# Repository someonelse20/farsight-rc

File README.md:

# Farsight RC

Custom long range remote controller with ESP32 to stream telemetry and an STM32 based lora module with the SX1262. The controller has a build in 18650 battery with an integrated charger. The transceiver is its own standalone board and can be used independenly of the controller. I made this project as a part of my larger goal to make a custom drone. I originally was going to make it out of stock modules but decided to design custom pcbs.

## Usage

**--This is still under development and is subject to change--**

### Controller

The switch in the middle of the controller is the power switch and the led is the status of the battery charging. The usb connecter will charge the battery and can be used to communicate with the ESP32. The micro SD card will log all the incoming telemetry.

The controller software is currently pretty basic and missing some fetures. The wifi network the esp32 will create can be configured by installing the espressive ide and running idf.py menuconfig and changing the wifi ssid and password under Wifi Configuration. Requesting /telemetry of the ip of the nextork will return a set of comma separated values in the format of "altitude_meters,speed_meters_per_second,heading_degrees,latitude,longitude".

### Transceiver

UART pinout:
| 1 | 2 | 3 | 4 |
|-----|-----|----|----|
| VCC | GND | RX | TX |

Microcontroller pinout:
| 1 | 2 |
|-------|------|
| RESET | BOOT |

Debug pinout:
| 1 | 2 |
|--------|-------|
| SWDCLK | SWDIO |

The transceiver has an internal regulator and can handle up to 5v input. The UART pinout is from the transceiver reference so an external device would put its Tx to the transceiver Rx and vice versa. The buttons on the board will put the STM32 into boot and reset mode respectively and the external pins are directly wired to the microcontroller.

The transceiver is built on the [Semtech SX1262 driver](https://github.com/Lora-net/sx126x_driver). To communicate with the transceiver a host must first send a register bit and then the data to transmit or receive based on the table below.
| Address | Name | Description | Input/Output | Size | Note |
|---------|--------------------------|------------------------------------|--------------|------|-------------------------------------------------------------------------------------------------------------------------------------------------------------------------|
| 0 | who_am_i | Device ID | O | 1 | Device ID is 126 |
| 1 | TX | Transmits packet | I | - | First send size byte then send data byte. |
| 2 | RX | Receives packet | I/O | - | First send size byte then send data byte. |
| 3 | TX_set | Transmits packet | I | - | Packet size must always be payload_len. |
| 4 | RX_set | Receives packet | O | - | Packet size must always be payload_len. |
| 5 | sleep | Puts transceiver into sleep mode | - | 0 | |
| 6 | wakeup | Wakes up transceiver | - | 0 | |
| 7 | set_all | Inputs a setting struct | I | TBD | See [settings_t](https://github.com/someonelse20/remote-controller/blob/main/software/transceiver/Core/Inc/uart_reg.h#L29) |
| 8 | set_frequency | Sets SX1262 frequency | I | 4 | See [sx126x_set_rf_freq](https://github.com/Lora-net/sx126x_driver/blob/master/src/sx126x.h#L1084) |
| 9 | set_tx_params | Sets SX1262 TX power and ramp time | I | 2 | array of {power in dBm, ramp time ([see datasheet](https://semtech.my.salesforce.com/sfc/p/#E0000000JelG/a/RQ000008nKCH/hp2iKwMDKWl34g1D3LBf_zC7TGBRIo2ff5LMnS8r19s]))} |
| 10 | set_lora_mod_params | Sets LoRa parameters | I | TBD | See [sx126x_mod_params_lora_t](https://github.com/Lora-net/sx126x_driver/blob/master/src/sx126x.h#L381) |
| 11 | set_lora_pkt_params | Sets LoRa packet parameters | I | TBD | See [sx126x_pkt_params_lora_t](https://github.com/Lora-net/sx126x_driver/blob/master/src/sx126x.h#L454) |
| 12 | set_lora_symb_nb_timeout | Sets loRa timeout in symbols | I | 1 | See [sx126x_set_lora_symb_nb_timeout](https://github.com/Lora-net/sx126x_driver/blob/master/src/sx126x.h#L1236) |
| 13 | set_encrypt_params | Sets encryption parameters | I | - | Not currently implemented |
| 14 | enable_encrypt | Enables/disables encryption | I | - | Not currently implemented |

TBD means that the size is based on the size of a struct which will be calculated when I can run the code on the hardware.

## BOM

BOM to make two transceivers and two controllers but with only two antennas and one micro SD card.
All prices in USD. Price column is total price and does not include shipping.
| Item | Quantity | Price | Link |
|------------------|----------|-------|--------------------------------------------------------------------------------------------------------|
| Controller pcb | 2 | 49.99 | https://jlcpcb.com |
| Transceiver | 2 | 87.36 | https://jlcpcb.com |
| RF filter | 2 | 0.92 | https://www.digikey.com/en/products/detail/johanson-technology-inc/0900FM15K0039001E/16639329 |
| ESP32-S3 | 2 | 5.28 | https://www.digikey.com/en/products/detail/espressif-systems/ESP32-S3-MINI-1-N8/15295890 |
| Thermistor | 2 | 0.20 | https://www.digikey.com/en/products/detail/tdk-corporation/NTCG103JF103FT1/614628 |
| Joystick | 2 | 6.08 | https://www.digikey.com/en/products/detail/c-k/THB001P/11687191 |
| RP-SMA connector | 2 | 7.40 | https://www.digikey.com/en/products/detail/taoglas-limited/PCB-RPSMAFRA-HT/5034735 |
| Antenna | 2 | 23.14 | https://www.digikey.com/en/products/detail/te-connectivity-linx/ANT-915-IPW1-RPS/15293389 |
| Power switch | 2 | 1.46 | https://www.digikey.com/en/products/detail/c-k/OS102011MS2QN1/411602 |
| Battery | 2 | 6.5 | https://www.18650batterystore.com/products/samsung-30q |
| Battery Holder | 2 | 5.56 | https://www.digikey.com/en/products/detail/mpd-memory-protection-devices/BK-18650-PC2/2079908 |
| MicroSD card | 1 | 9.99 | https://www.amazon.com/Adapter-Memory-Tablet-Console-TF162/dp/B0CYT2KL98 |
| ST-Link V2 | 1 | 9.49 | https://www.amazon.com/HiLetgo-Emulator-Downloader-Programmer-STM32F103C8T6/dp/B07SQV6VLZ |
| OLED display | 1 | 6.99 | https://www.amazon.com/UCTRONICS-SSD1306-Self-Luminous-Display-Raspberry/dp/B072Q2X2LL |

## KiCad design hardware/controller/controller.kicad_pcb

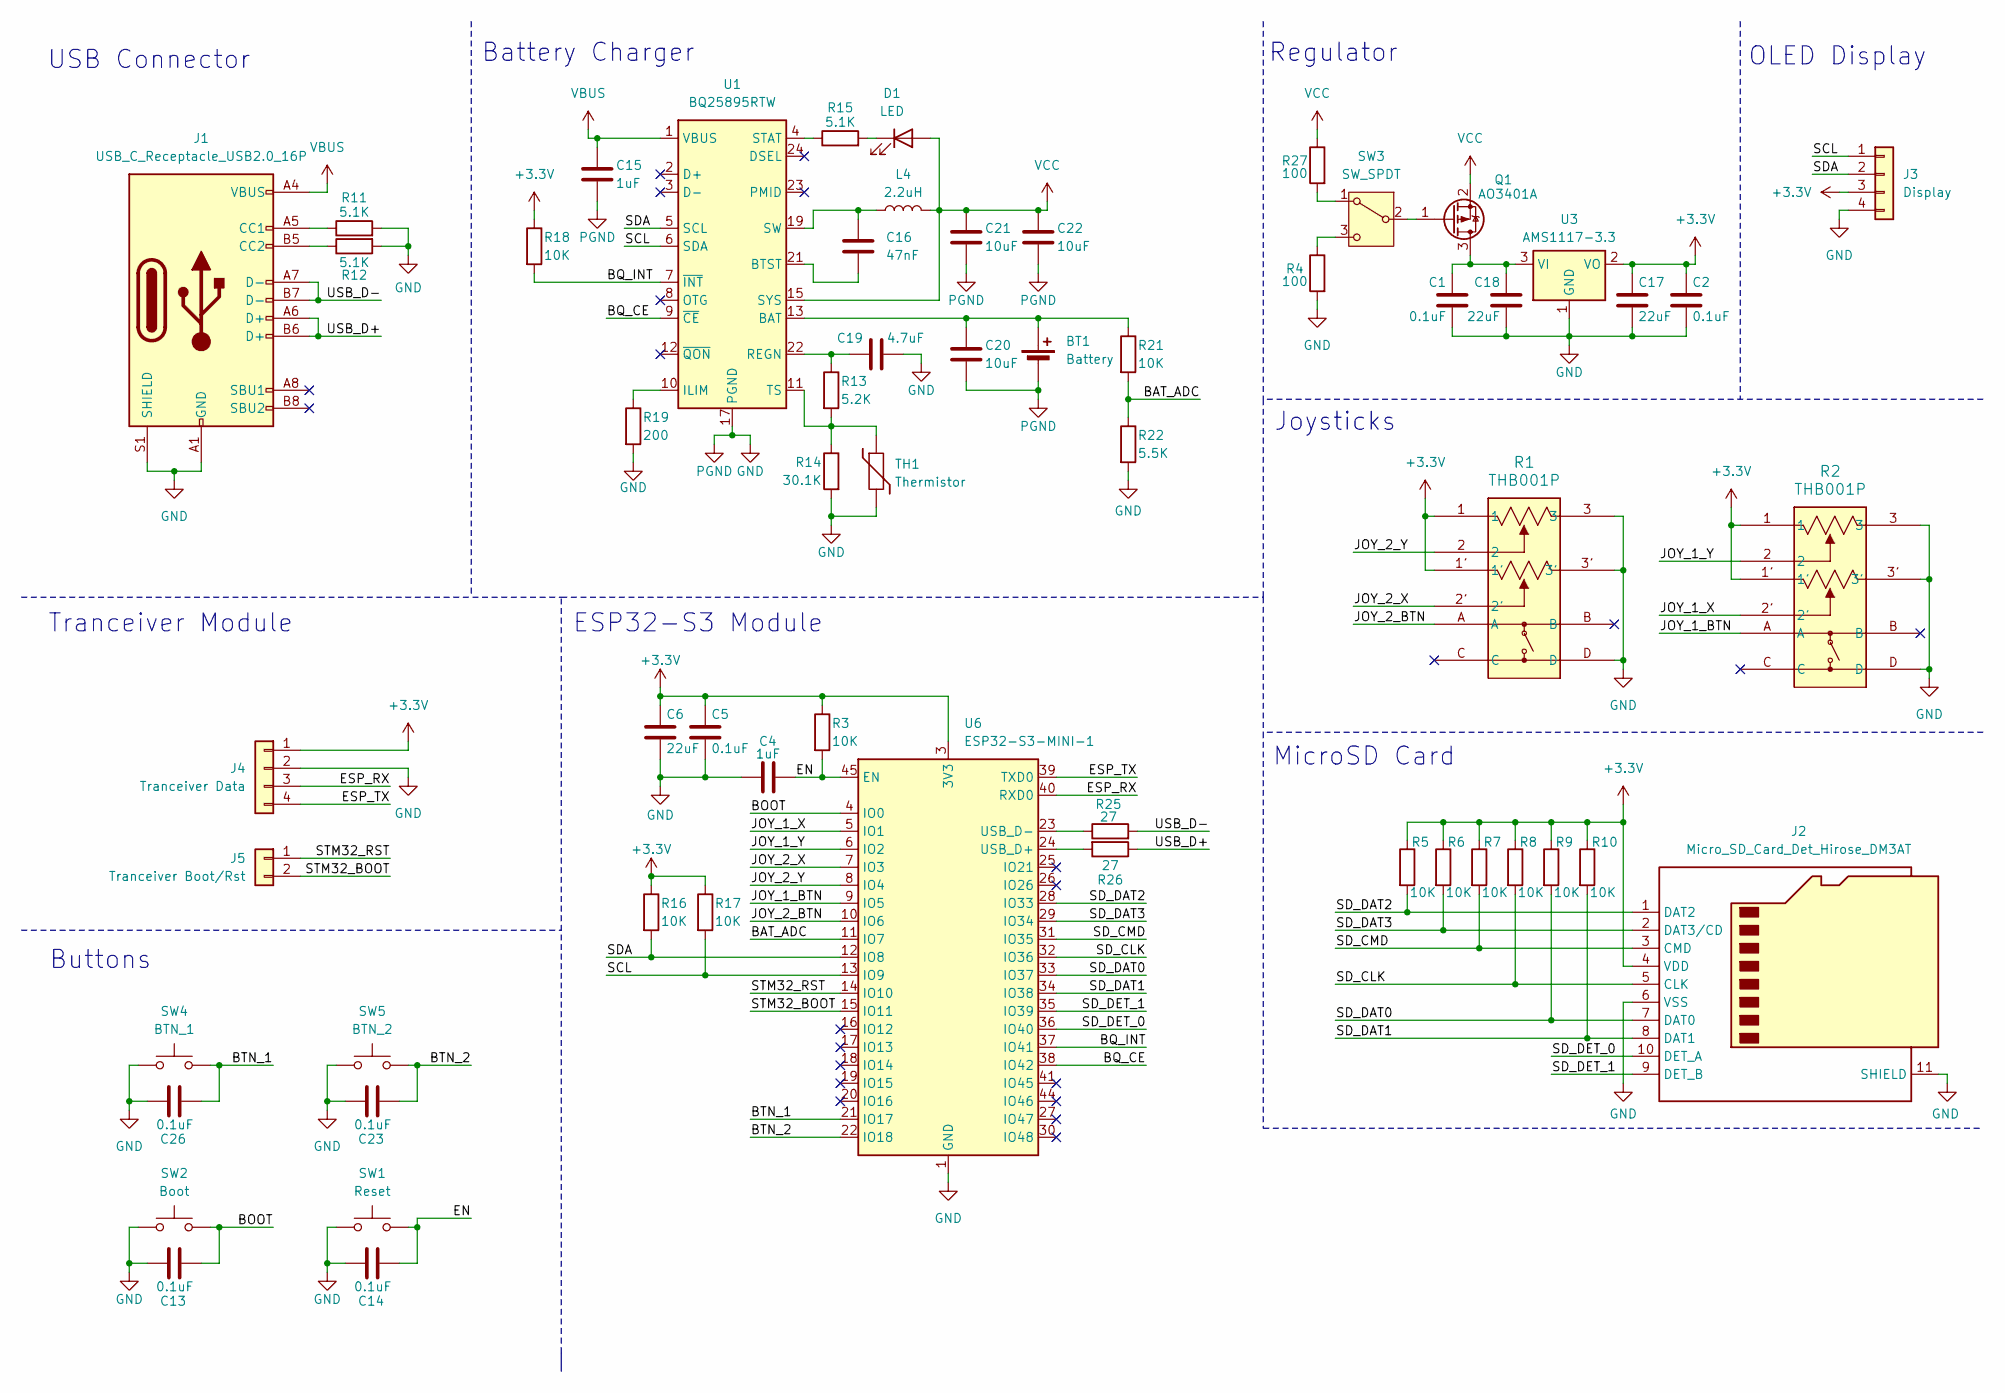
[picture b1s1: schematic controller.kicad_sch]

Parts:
BT1: Battery; BatteryHolder_MPD_BH-18650-PC
C1, C2, C5, C13, C14, C23, C26: 0.1uF; C_0402_1005Metric
C4, C15: 1uF; C_0402_1005Metric
C6, C17, C18: 22uF; C_0603_1608Metric
C16: 47nF; C_0402_1005Metric
C19: 4.7uF; C_0402_1005Metric
C20, C21, C22: 10uF; C_0603_1608Metric
D1: LED; LED_D5.0mm
J1: USB_C_Receptacle_USB2.0_16P; USB_C_Receptacle_GCT_USB4105-xx-A_16P_TopMnt_Horizontal
J2: Micro_SD_Card_Det_Hirose_DM3AT; microSD_HC_Hirose_DM3AT-SF-PEJM5
J3: Display; JST_XH_B4B-XH-A_1x04_P2.50mm_Vertical
J4: Tranceiver Data; JST_XH_B4B-XH-A_1x04_P2.50mm_Vertical
J5: Tranceiver Boot/Rst; JST_XH_B2B-XH-A_1x02_P2.50mm_Vertical
L4: 2.2uH; L_6.3x6.3_H3
Q1: AO3401A; SOT-23
R1, R2: THB001P; THB001P_CNK
R3, R5, R6, R7, R8, R9, R10, R16, R17, R18, R21: 10K; R_0402_1005Metric
R4, R27: 100; R_0402_1005Metric
R11, R12, R15: 5.1K; R_0402_1005Metric
R13: 5.2K; R_0402_1005Metric
R14: 30.1K; R_0402_1005Metric
R19: 200; R_0402_1005Metric
R22: 5.5K; R_0402_1005Metric
R25, R26: 27; R_0402_1005Metric
SW1: Reset; SW_Push_SPST_NO_Alps_SKRK
SW2: Boot; SW_Push_SPST_NO_Alps_SKRK
SW3: SW_SPDT; SW_Slide_SPDT_Straight_CK_OS102011MS2Q
SW4: BTN_1; SolderWire-0.1sqmm_1x02_P3.6mm_D0.4mm_OD1mm
SW5: BTN_2; SolderWire-0.1sqmm_1x02_P3.6mm_D0.4mm_OD1mm
TH1: Thermistor; R_0201_0603Metric
U1: BQ25895RTW; Texas_RTW_WQFN-24-1EP_4x4mm_P0.5mm_EP2.7x2.7mm_ThermalVias
U3: AMS1117-3.3; SOT-223-3_TabPin2
U6: ESP32-S3-MINI-1; ESP32-S2-MINI-1

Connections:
+3.3V: C2.1, C5.1, C6.1, C17.1, J2.4 (VDD), J3.3, J4.1, R1.1, R1.1', R2.1, R2.1', R3.1, R5.1, R6.1, R7.1, R8.1, R9.1, R10.1, R16.1, R17.1, R18.1, U3.2 (VO), U6.3 (3V3)
/BAT_ADC: R21.2, R22.1, U6.11 (IO7)
/BOOT: C13.2, SW2.2, U6.4 (IO0)
/BQ_CE: U1.9 (~CE), U6.38 (IO42)
/BQ_INT: R18.2, U1.7 (~INT), U6.37 (IO41)
/BTN_1: C26.2, SW4.2, U6.21 (IO17)
/BTN_2: C23.2, SW5.2, U6.22 (IO18)
/EN: C4.2, C14.2, R3.2, SW1.2, U6.45 (EN)
/ESP_RX: J4.3, U6.40 (RXD0)
/ESP_TX: J4.4, U6.39 (TXD0)
/JOY_1_BTN: R2.A, U6.9 (IO5)
/JOY_1_X: R2.2', U6.5 (IO1)
/JOY_1_Y: R2.2, U6.6 (IO2)
/JOY_2_BTN: R1.A, U6.10 (IO6)
/JOY_2_X: R1.2', U6.7 (IO3)
/JOY_2_Y: R1.2, U6.8 (IO4)
/SCL: J3.1, R17.2, U1.6 (SDA), U6.13 (IO9)
/SDA: J3.2, R16.2, U1.5 (SCL), U6.12 (IO8)
/SD_CLK: J2.5 (CLK), R8.2, U6.32 (IO36)
/SD_CMD: J2.3 (CMD), R7.2, U6.31 (IO35)
/SD_DAT0: J2.7 (DAT0), R9.2, U6.33 (IO37)
/SD_DAT1: J2.8 (DAT1), R10.2, U6.34 (IO38)
/SD_DAT2: J2.1 (DAT2), R5.2, U6.28 (IO33)
/SD_DAT3: J2.2 (DAT3/CD), R6.2, U6.29 (IO34)
/SD_DET_0: J2.10 (DET_A), U6.36 (IO40)
/SD_DET_1: J2.9 (DET_B), U6.35 (IO39)
/STM32_BOOT: J5.2, U6.15 (IO11)
/STM32_RST: J5.1, U6.14 (IO10)
/USB_D+: J1.A6 (D+), J1.B6 (D+), R26.1
/USB_D-: J1.A7 (D-), J1.B7 (D-), R25.2
GND: BT1.2 (-), C1.2, C2.2, C4.1, C5.2, C6.2, C13.1, C14.1, C15.2, C17.2, C18.2, C19.2, C20.2, C21.2, C22.2, C23.1, C26.1, J1.A1 (GND), J1.A12 (GND), J1.B1 (GND), J1.B12 (GND), J1.S1 (SHIELD), J2.6 (VSS), J2.11 (SHIELD), J3.4, J4.2, R1.3, R1.3', R1.D, R2.3, R2.3', R2.D, R4.2, R11.2, R12.2, R14.2, R19.2, R22.2, SW1.1, SW2.1, SW4.1, SW5.1, TH1.2, U1.17 (PGND), U1.18 (PGND), U1.25 (PGND), U3.1 (GND), U6.1 (GND), U6.2 (GND), U6.42 (GND), U6.43 (GND), U6.46 (GND), U6.47 (GND), U6.48 (GND), U6.49 (GND), U6.50 (GND), U6.51 (GND), U6.52 (GND), U6.53 (GND), U6.54 (GND), U6.55 (GND), U6.56 (GND), U6.57 (GND), U6.58 (GND), U6.59 (GND), U6.60 (GND), U6.61 (GND), U6.62 (GND), U6.63 (GND), U6.64 (GND), U6.65 (GND)
unnamed: BT1.1 (+), C20.1, R21.1, U1.13 (BAT), U1.14 (BAT)
unnamed: C16.1, L4.1, U1.19 (SW), U1.20 (SW)
unnamed: D1.1 (K), R15.2
unnamed: J1.A5 (CC1), R11.1
unnamed: J1.B5 (CC2), R12.1
unnamed: C1.1, C18.1, Q1.3 (D), U3.3 (VI)
unnamed: Q1.1 (G), SW3.2 (B)
unnamed: R27.2, SW3.1 (A)
unnamed: R4.1, SW3.3 (C)
unnamed: C16.2, U1.21 (BTST)
unnamed: R19.1, U1.10 (ILIM)
unnamed: C19.1, R13.1, U1.22 (REGN)
unnamed: R15.1, U1.4 (STAT)
unnamed: R13.2, R14.1, TH1.1, U1.11 (TS)
unnamed: R26.2, U6.24 (USB_D+)
unnamed: R25.1, U6.23 (USB_D-)
VBUS: C15.1, J1.A4 (VBUS), J1.A9 (VBUS), J1.B4 (VBUS), J1.B9 (VBUS), U1.1 (VBUS)
VCC: C21.1, C22.1, D1.2 (A), L4.2, Q1.2 (S), R27.1, U1.15 (SYS), U1.16 (SYS)

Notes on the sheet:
Regulator
ESP32-S3 Module
Joysticks
Buttons
USB Connector
Battery Charger
Tranceiver Module
OLED Display
MicroSD Card

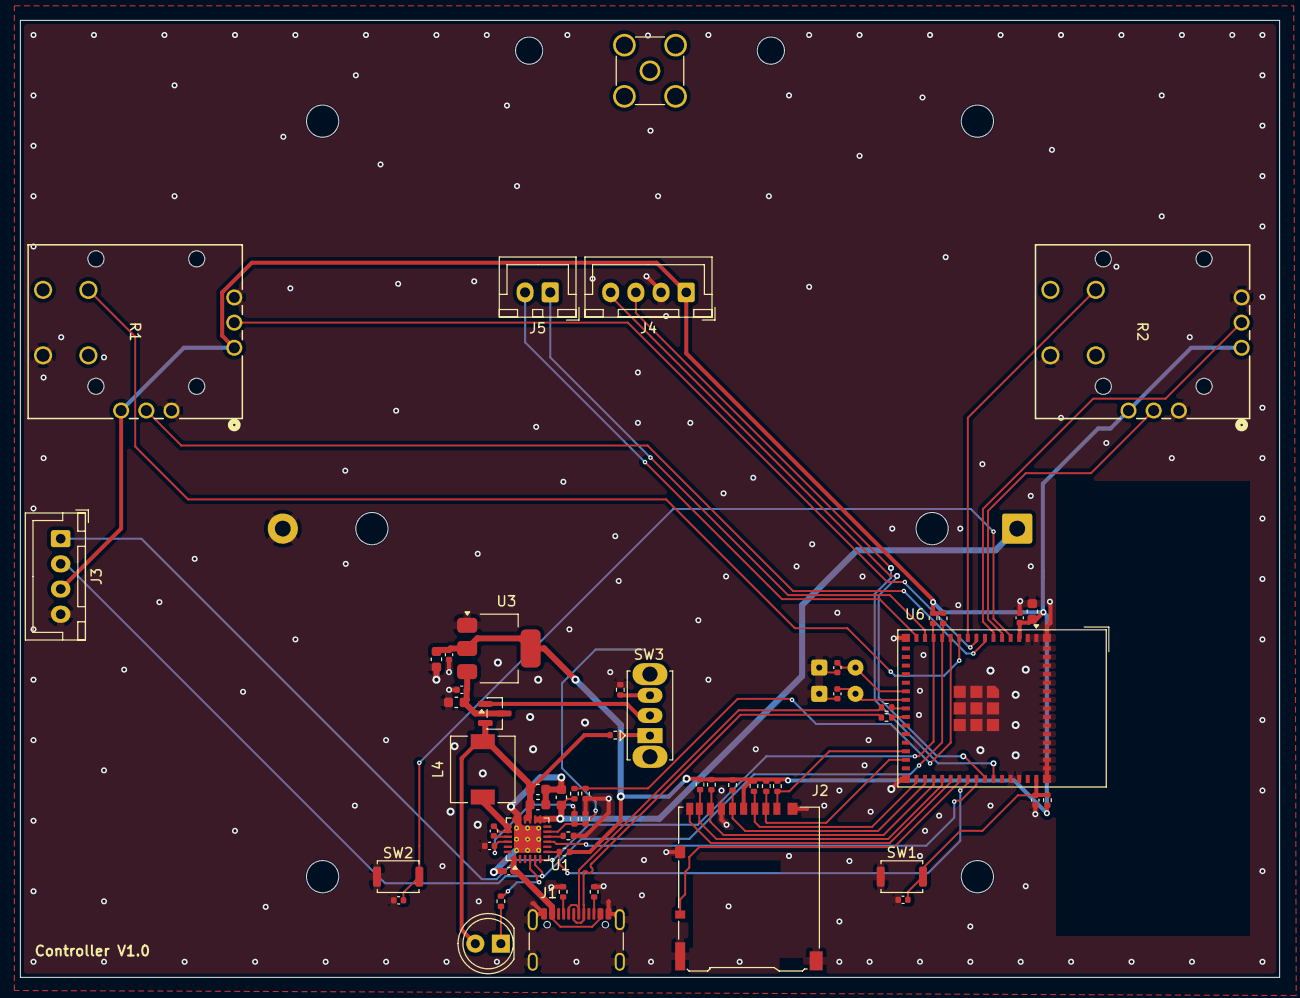
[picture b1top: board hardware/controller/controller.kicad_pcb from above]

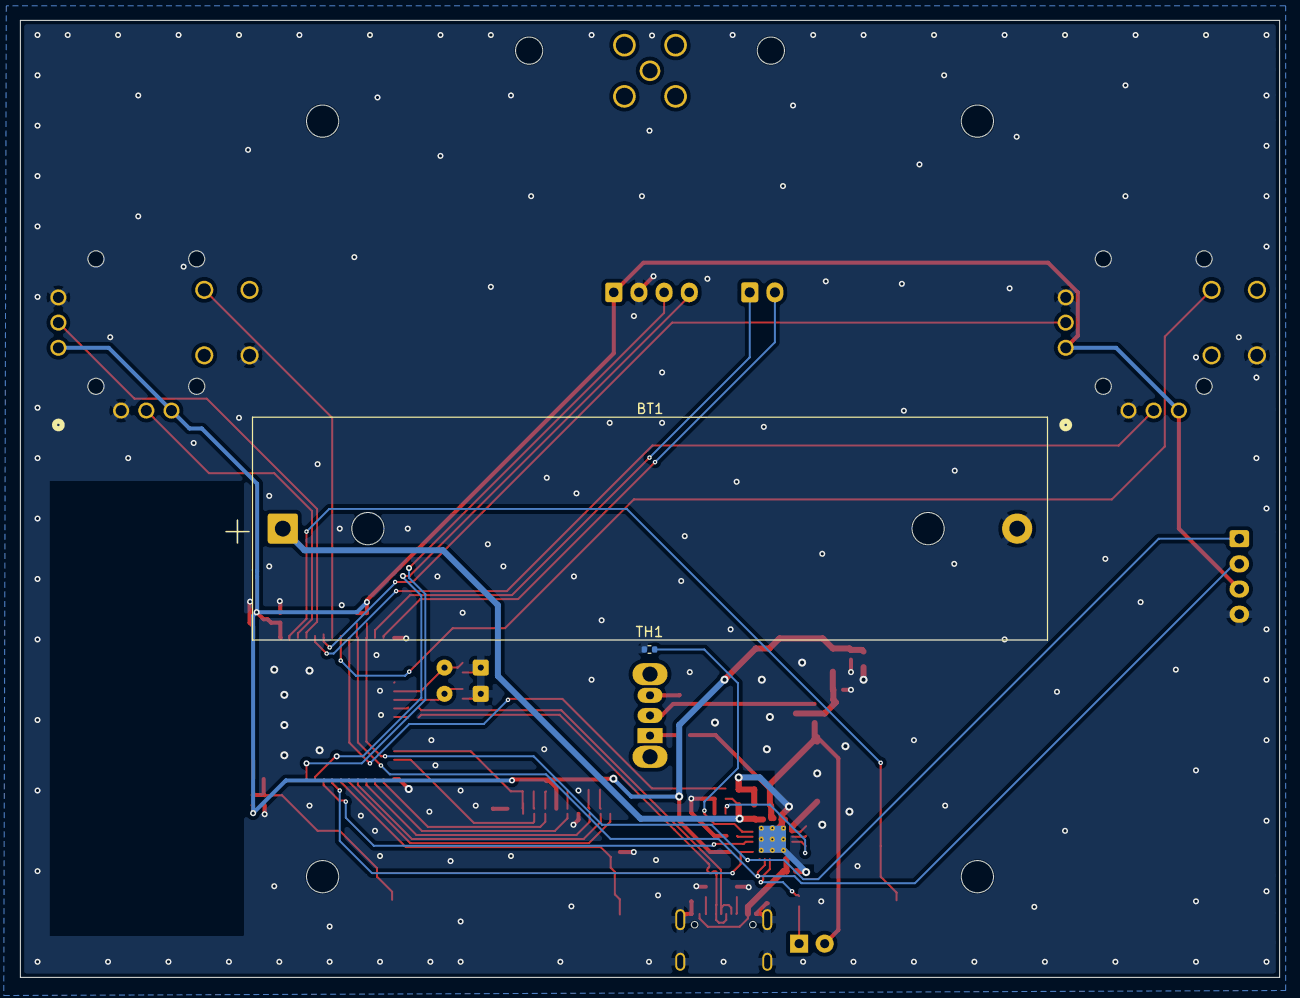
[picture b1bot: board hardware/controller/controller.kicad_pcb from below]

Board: 2 copper layers, 125.0 x 95.0 mm, 59 parts (2 on the bottom side), 49 nets.

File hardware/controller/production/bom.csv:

Designator,Footprint,Quantity,Value,LCSC Part #
BT1,BatteryHolder_MPD_BH-18650-PC,1,Battery,
"C1, C13, C14, C2, C23, C26, C5",0402,7,0.1uF,
"C15, C4",0402,2,1uF,
C16,0402,1,47nF,
"C17, C18, C6",0603,3,22uF,
C19,0402,1,4.7uF,
"C20, C21, C22",0603,3,10uF,
D1,LED_D5.0mm,1,LED,
J1,USB_C_Receptacle_GCT_USB4105-xx-A_16P_TopMnt_Horizontal,1,USB_C_Receptacle_USB2.0_16P,
J2,microSD_HC_Hirose_DM3AT-SF-PEJM5,1,Micro_SD_Card_Det_Hirose_DM3AT,
J3,JST_XH_B4B-XH-A_1x04_P2.50mm_Vertical,1,Display,
J4,JST_XH_B4B-XH-A_1x04_P2.50mm_Vertical,1,Tranceiver Data,
J5,JST_XH_B2B-XH-A_1x02_P2.50mm_Vertical,1,Tranceiver Boot/Rst,
L4,L_6.3x6.3_H3,1,2.2uH,
Q1,SOT-23,1,AO3401A,
"R1, R2",THB001P_CNK,2,THB001P,
"R10, R16, R17, R18, R21, R3, R5, R6, R7, R8, R9",0402,11,10K,
"R11, R12, R15",0402,3,5.1K,
R13,0402,1,5.2K,
R14,0402,1,30.1K,
R19,0402,1,200,
R22,0402,1,5.5K,
"R25, R26",0402,2,27,
"R27, R4",0402,2,100,
SW1,SW_Push_SPST_NO_Alps_SKRK,1,Reset,
SW2,SW_Push_SPST_NO_Alps_SKRK,1,Boot,
SW3,SW_Slide_SPDT_Straight_CK_OS102011MS2Q,1,SW_SPDT,
SW4,SolderWire-0.1sqmm_1x02_P3.6mm_D0.4mm_OD1mm,1,BTN_1,
SW5,SolderWire-0.1sqmm_1x02_P3.6mm_D0.4mm_OD1mm,1,BTN_2,
TH1,0402,1,Thermistor,
U1,Texas_RTW_WQFN-24-1EP_4x4mm_P0.5mm_EP2.7x2.7mm_ThermalVias,1,BQ25895RTW,
U3,SOT-223-3_TabPin2,1,AMS1117-3.3,
U6,ESP32-S2-MINI-1,1,ESP32-S3-MINI-1,

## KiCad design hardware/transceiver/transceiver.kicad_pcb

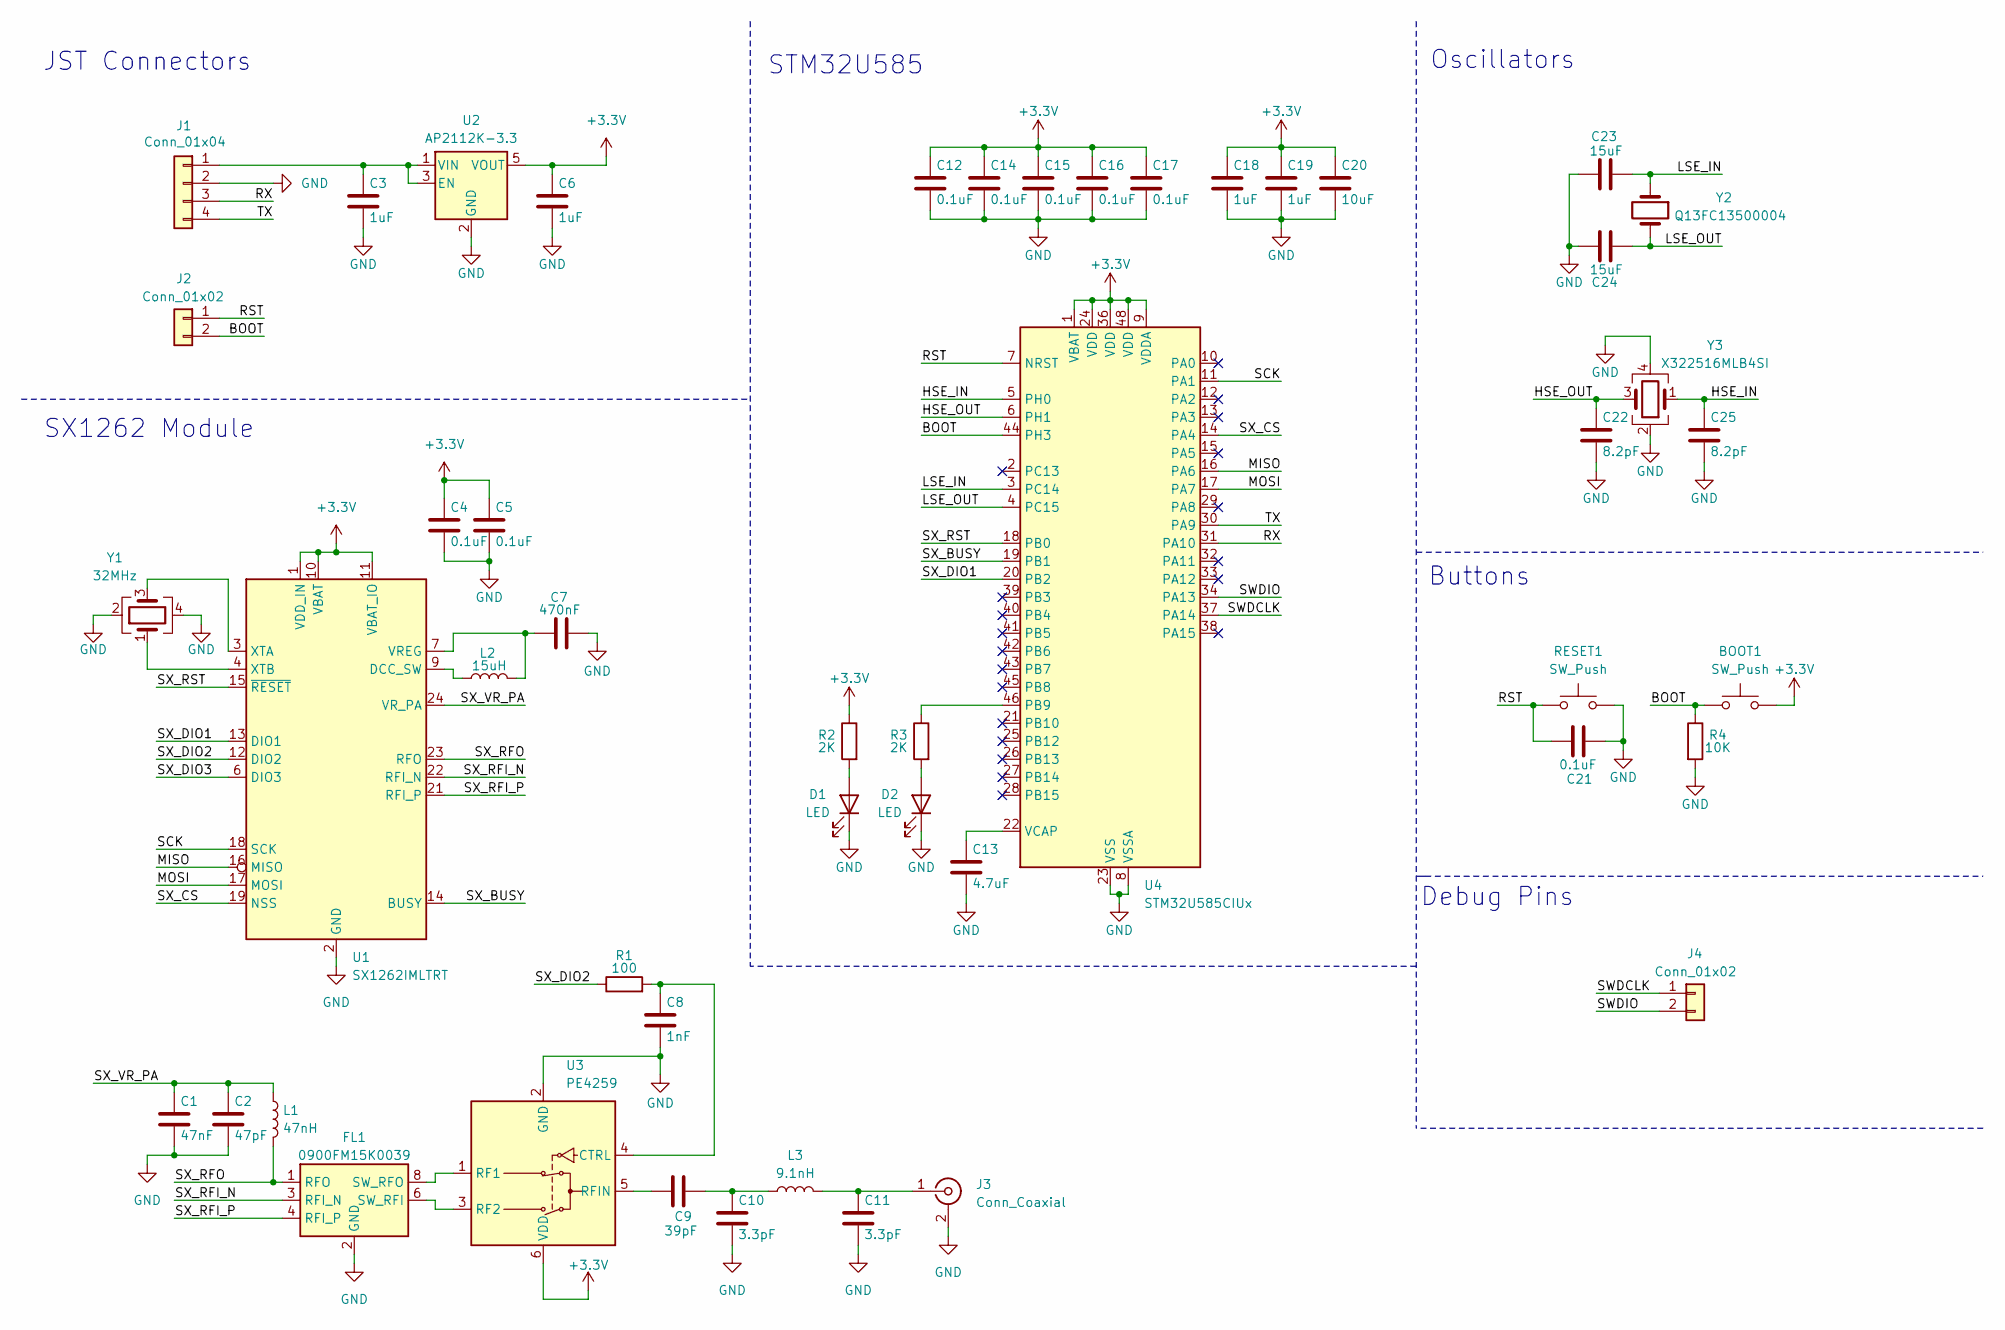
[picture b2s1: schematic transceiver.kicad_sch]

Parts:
BOOT1: SW_Push; SW_Push_SPST_NO_Alps_SKRK
C1: 47nF; C_0402_1005Metric
C2: 47pF; C_0402_1005Metric
C3, C6, C18, C19: 1uF; C_0603_1608Metric
C4, C5, C12, C14, C15, C16, C17, C21: 0.1uF; C_0402_1005Metric
C7: 470nF; C_0402_1005Metric
C8: 1nF; C_0402_1005Metric
C9: 39pF; C_0402_1005Metric
C10, C11: 3.3pF; C_0402_1005Metric
C13: 4.7uF; C_0402_1005Metric
C20: 10uF; C_0603_1608Metric
C22, C25: 8.2pF; C_0402_1005Metric
C23, C24: 15uF; C_0402_1005Metric
D1, D2: LED; LED_0603_1608Metric
FL1: 0900FM15K0039; Balun_Johanson_0900FM15K0039
J1: Conn_01x04; JST_XH_B4B-XH-A_1x04_P2.50mm_Vertical
J2: Conn_01x02; JST_XH_B2B-XH-A_1x02_P2.50mm_Vertical
J3: Conn_Coaxial; SMA_Amphenol_901-144_Vertical
J4: Conn_01x02; PinHeader_1x02_P2.54mm_Vertical
L1: 47nH; L_0402_1005Metric
L2: 15uH; L_0603_1608Metric
L3: 9.1nH; L_0402_1005Metric
R1: 100; R_0402_1005Metric
R2, R3: 2K; R_0402_1005Metric
R4: 10K; R_0402_1005Metric
RESET1: SW_Push; SW_Push_SPST_NO_Alps_SKRK
U1: SX1262IMLTRT; QFN-24-1EP_4x4mm_P0.5mm_EP2.6x2.6mm
U2: AP2112K-3.3; SOT-23-5
U3: PE4259; SOT-363_SC-70-6
U4: STM32U585CIUx; QFN-48-1EP_7x7mm_P0.5mm_EP5.6x5.6mm
Y1: 32MHz; Crystal_SMD_3225-4Pin_3.2x2.5mm
Y2: Q13FC13500004; Crystal_SMD_3215-2Pin_3.2x1.5mm
Y3: X322516MLB4SI; Crystal_SMD_3225-4Pin_3.2x2.5mm

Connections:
+3.3V: BOOT1.1, C4.1, C5.1, C6.1, C12.1, C14.1, C15.1, C16.1, C17.1, C18.1, C19.1, C20.1, R2.1, U1.1 (VDD_IN), U1.10 (VBAT), U1.11 (VBAT_IO), U2.5 (VOUT), U3.6 (VDD), U4.1 (VBAT), U4.9 (VDDA), U4.24 (VDD), U4.36 (VDD), U4.48 (VDD)
/BOOT: BOOT1.2, J2.2, R4.1, U4.44 (PH3)
/HSE_IN: C25.1, U4.5 (PH0), Y3.1
/HSE_OUT: C22.1, U4.6 (PH1), Y3.3
/LSE_IN: C23.2, U4.3 (PC14), Y2.1
/LSE_OUT: C24.1, U4.4 (PC15), Y2.2
/MISO: U1.16 (MISO), U4.16 (PA6)
/MOSI: U1.17 (MOSI), U4.17 (PA7)
/RST: C21.2, J2.1, RESET1.2, U4.7 (NRST)
/RX: J1.3, U4.31 (PA10)
/SCK: U1.18 (SCK), U4.11 (PA1)
/SWDCLK: J4.1, U4.37 (PA14)
/SWDIO: J4.2, U4.34 (PA13)
/SX_BUSY: U1.14 (BUSY), U4.19 (PB1)
/SX_CS: U1.19 (NSS), U4.14 (PA4)
/SX_DIO1: U1.13 (DIO1), U4.20 (PB2)
/SX_DIO2: R1.1, U1.12 (DIO2)
/SX_DIO3: U1.6 (DIO3)
/SX_RFI_N: FL1.3 (RFI_N), U1.22 (RFI_N)
/SX_RFI_P: FL1.4 (RFI_P), U1.21 (RFI_P)
/SX_RFO: FL1.1 (RFO), L1.2, U1.23 (RFO)
/SX_RST: U1.15 (~RESET), U4.18 (PB0)
/SX_VR_PA: C1.1, C2.1, L1.1, U1.24 (VR_PA)
/TX: J1.4, U4.30 (PA9)
GND: C1.2, C2.2, C3.2, C4.2, C5.2, C6.2, C7.2, C8.2, C10.2, C11.2, C12.2, C13.2, C14.2, C15.2, C16.2, C17.2, C18.2, C19.2, C20.2, C21.1, C22.2, C23.1, C24.2, C25.2, D1.1 (K), D2.1 (K), FL1.2 (GND), FL1.5 (GND), FL1.7 (GND), FL1.9 (GND), FL1.10 (GND), J1.2, J3.2 (Ext), R4.2, RESET1.1, U1.2 (GND), U1.5 (GND), U1.8 (GND), U1.20 (GND), U1.25 (GND), U2.2 (GND), U3.2 (GND), U4.8 (VSSA), U4.23 (VSS), U4.35 (VSS), U4.47 (VSS), U4.49 (VSS), Y1.2, Y1.4, Y3.2, Y3.4
unnamed: C9.2, C10.1, L3.1
unnamed: D1.2 (A), R2.2
unnamed: D2.2 (A), R3.2
unnamed: FL1.6 (SW_RFI), U3.3 (RF2)
unnamed: FL1.8 (SW_RFO), U3.1 (RF1)
unnamed: C3.1, J1.1, U2.1 (VIN), U2.3 (EN)
unnamed: C11.1, J3.1 (In), L3.2
unnamed: L2.1, U1.9 (DCC_SW)
unnamed: C7.1, L2.2, U1.7 (VREG)
unnamed: U1.3 (XTA), Y1.3
unnamed: U1.4 (XTB), Y1.1
unnamed: C8.1, R1.2, U3.4 (CTRL)
unnamed: C9.1, U3.5 (RFIN)
unnamed: R3.1, U4.46 (PB9)
unnamed: C13.1, U4.22 (VCAP)

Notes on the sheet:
STM32U585
Buttons
SX1262 Module
Debug Pins
JST Connectors
Oscillators

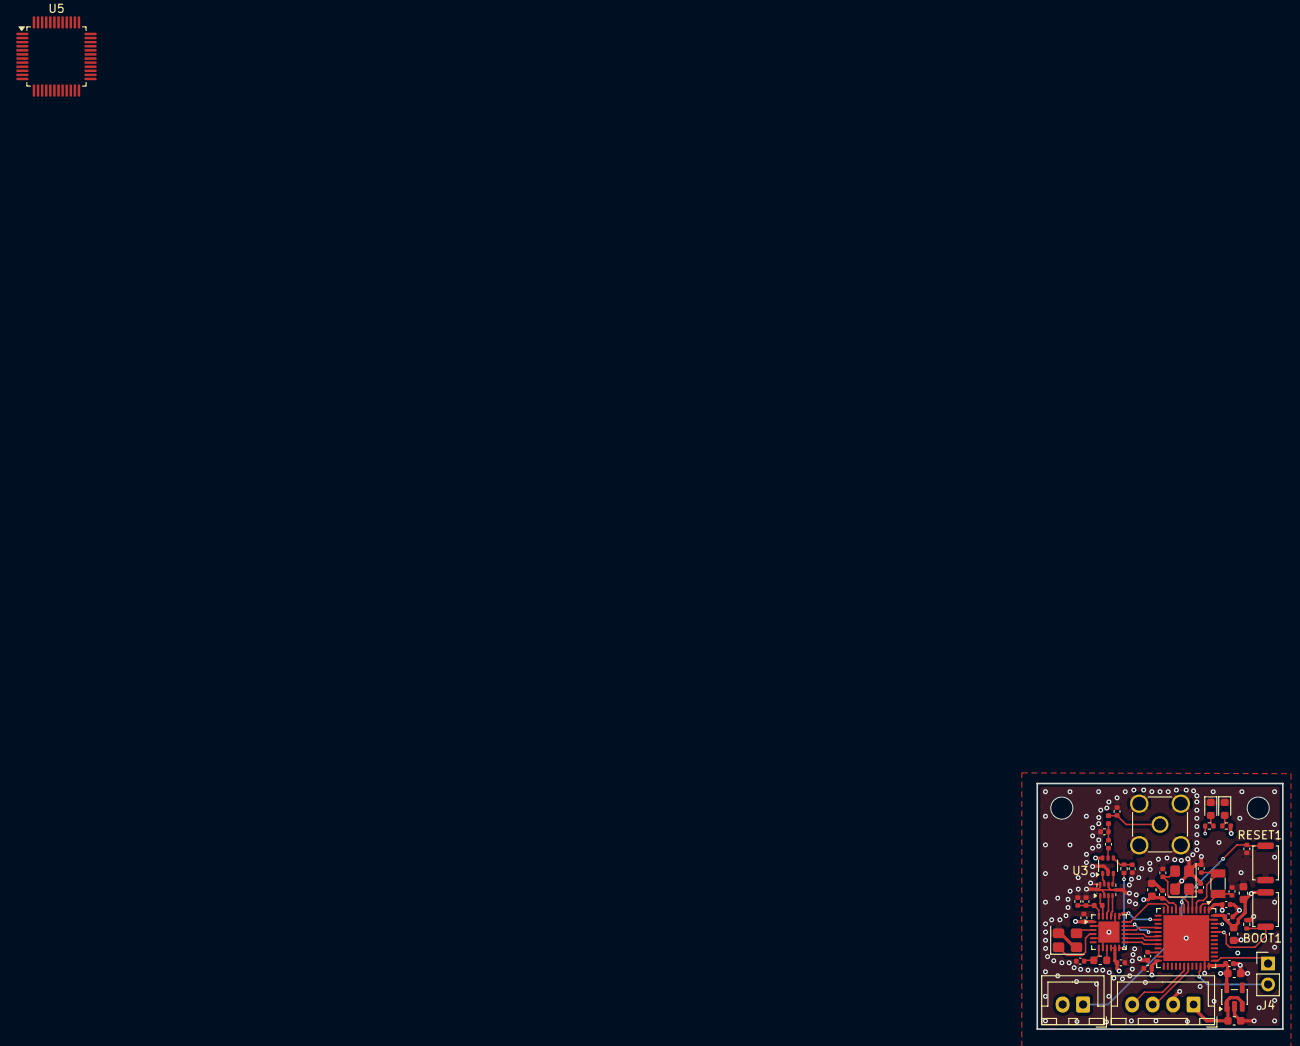
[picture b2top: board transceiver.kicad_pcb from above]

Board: 4 copper layers, 30.0 x 30.0 mm, 49 parts (0 on the bottom side), 40 nets.

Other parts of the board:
U5: STM32U585CITx; LQFP-48_7x7mm_P0.5mm

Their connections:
unnamed: U5.23 (VSS), U5.35 (VSS), U5.47 (VSS)

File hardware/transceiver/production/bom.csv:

Designator,Footprint,Quantity,Value,LCSC Part #
"BOOT, RESET",SW_Push_SPST_NO_Alps_SKRK,2,SW_Push,
C1,0402,1,47nF,
"C10, C11",0402,2,3.3pF,
"C12, C14, C15, C16, C17, C21, C4, C5",0402,8,0.1uF,
C13,0402,1,4.7uF,
"C18, C19, C3, C6",0603,4,1uF,
C2,0402,1,47pF,
C20,0603,1,10uF,
"C22, C25",0402,2,8.2pF,
"C23, C24",0402,2,15uF,
C7,0402,1,470nF,
C8,0402,1,1nF,
C9,0402,1,39pF,
"D1, D2",0603,2,LED,
FL1,Balun_Johanson_0900FM15K0039,1,0900FM15K0039,
J1,JST_XH_B4B-XH-A_1x04_P2.50mm_Vertical,1,Conn_01x04,
J2,JST_XH_B2B-XH-A_1x02_P2.50mm_Vertical,1,Conn_01x02,
J3,SMA_Amphenol_901-144_Vertical,1,Conn_Coaxial,
J4,PinHeader_1x02_P2.54mm_Vertical,1,Conn_01x02,
L1,0402,1,47nH,
L2,0603,1,15uH,
L3,0402,1,9.1nH,
R1,0402,1,100,
"R2, R3",0402,2,2K,
R4,0402,1,10K,
U1,QFN-24-1EP_4x4mm_P0.5mm_EP2.6x2.6mm,1,SX1262IMLTRT,
U2,SOT-23-5,1,AP2112K-3.3,
U3,SOT-363_SC-70-6,1,PE4259,
U4,QFN-48-1EP_7x7mm_P0.5mm_EP5.6x5.6mm,1,STM32U585CIUx,
Y1,Crystal_SMD_3225-4Pin_3.2x2.5mm,1,32MHz,
Y2,Crystal_SMD_3215-2Pin_3.2x1.5mm,1,Q13FC13500004,
Y3,Crystal_SMD_3225-4Pin_3.2x2.5mm,1,X322516MLB4SI,

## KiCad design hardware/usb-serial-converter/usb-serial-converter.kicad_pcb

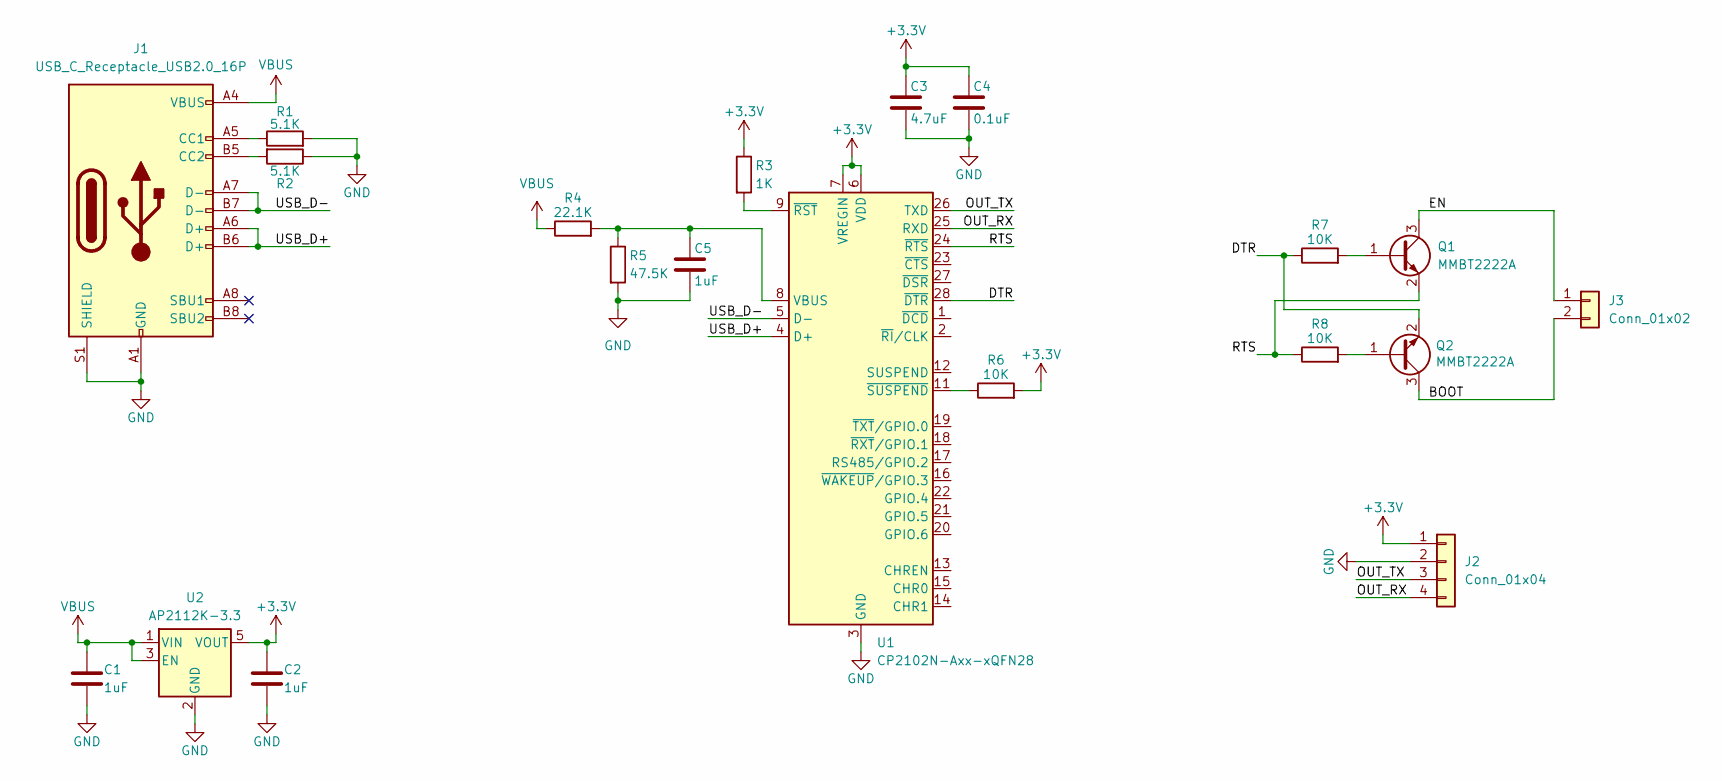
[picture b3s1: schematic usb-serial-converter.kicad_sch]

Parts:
C1, C2, C5: 1uF; C_0402_1005Metric
C3: 4.7uF; C_0603_1608Metric
C4: 0.1uF; C_0402_1005Metric
J1: USB_C_Receptacle_USB2.0_16P; USB_C_Receptacle_GCT_USB4105-xx-A_16P_TopMnt_Horizontal
J2: Conn_01x04; JST_XH_B4B-XH-A_1x04_P2.50mm_Vertical
J3: Conn_01x02; JST_XH_B2B-XH-A_1x02_P2.50mm_Vertical
Q1, Q2: MMBT2222A; SOT-23
R1, R2: 5.1K; R_0402_1005Metric
R3: 1K; R_0402_1005Metric
R4: 22.1K; R_0402_1005Metric
R5: 47.5K; R_0402_1005Metric
R6, R7, R8: 10K; R_0402_1005Metric
U1: CP2102N-Axx-xQFN28; QFN-28-1EP_5x5mm_P0.5mm_EP3.35x3.35mm
U2: AP2112K-3.3; SOT-23-5

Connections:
+3.3V: C2.1, C3.1, C4.1, J2.1, R3.1, R6.2, U1.6 (VDD), U1.7 (VREGIN), U2.5 (VOUT)
/BOOT: J3.2, Q2.3 (C)
/DTR: Q2.2 (E), R7.1, U1.28 (~DTR)
/EN: J3.1, Q1.3 (C)
/OUT_RX: J2.4, U1.25 (RXD)
/OUT_TX: J2.3, U1.26 (TXD)
/RTS: Q1.2 (E), R8.1, U1.24 (~RTS)
/USB_D+: J1.A6 (D+), J1.B6 (D+), U1.4 (D+)
/USB_D-: J1.A7 (D-), J1.B7 (D-), U1.5 (D-)
GND: C1.2, C2.2, C3.2, C4.2, C5.2, J1.A1 (GND), J1.A12 (GND), J1.B1 (GND), J1.B12 (GND), J1.S1 (SHIELD), J2.2, R1.2, R2.1, R5.2, U1.3 (GND), U1.29 (GND), U2.2 (GND)
unnamed: J1.A5 (CC1), R1.1
unnamed: J1.B5 (CC2), R2.2
unnamed: Q1.1 (B), R7.2
unnamed: Q2.1 (B), R8.2
unnamed: C5.1, R4.2, R5.1, U1.8 (VBUS)
unnamed: R3.2, U1.9 (~RST)
unnamed: R6.1, U1.11 (~SUSPEND)
VBUS: C1.1, J1.A4 (VBUS), J1.A9 (VBUS), J1.B4 (VBUS), J1.B9 (VBUS), R4.1, U2.1 (VIN), U2.3 (EN)

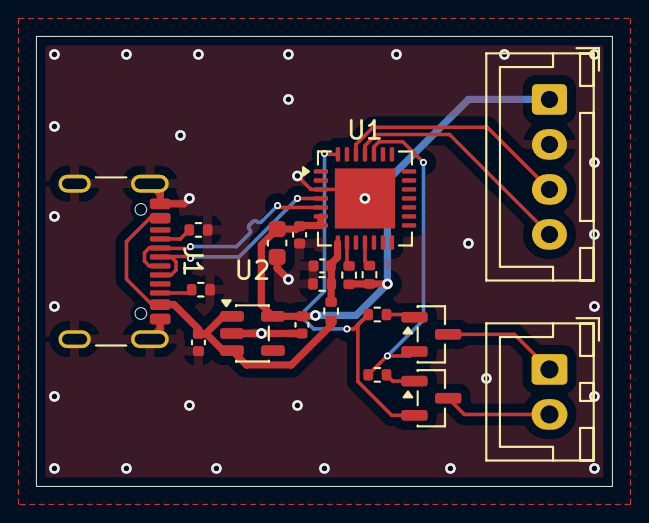
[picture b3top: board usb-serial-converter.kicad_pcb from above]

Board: 2 copper layers, 32.0 x 25.0 mm, 20 parts (0 on the bottom side), 18 nets.
